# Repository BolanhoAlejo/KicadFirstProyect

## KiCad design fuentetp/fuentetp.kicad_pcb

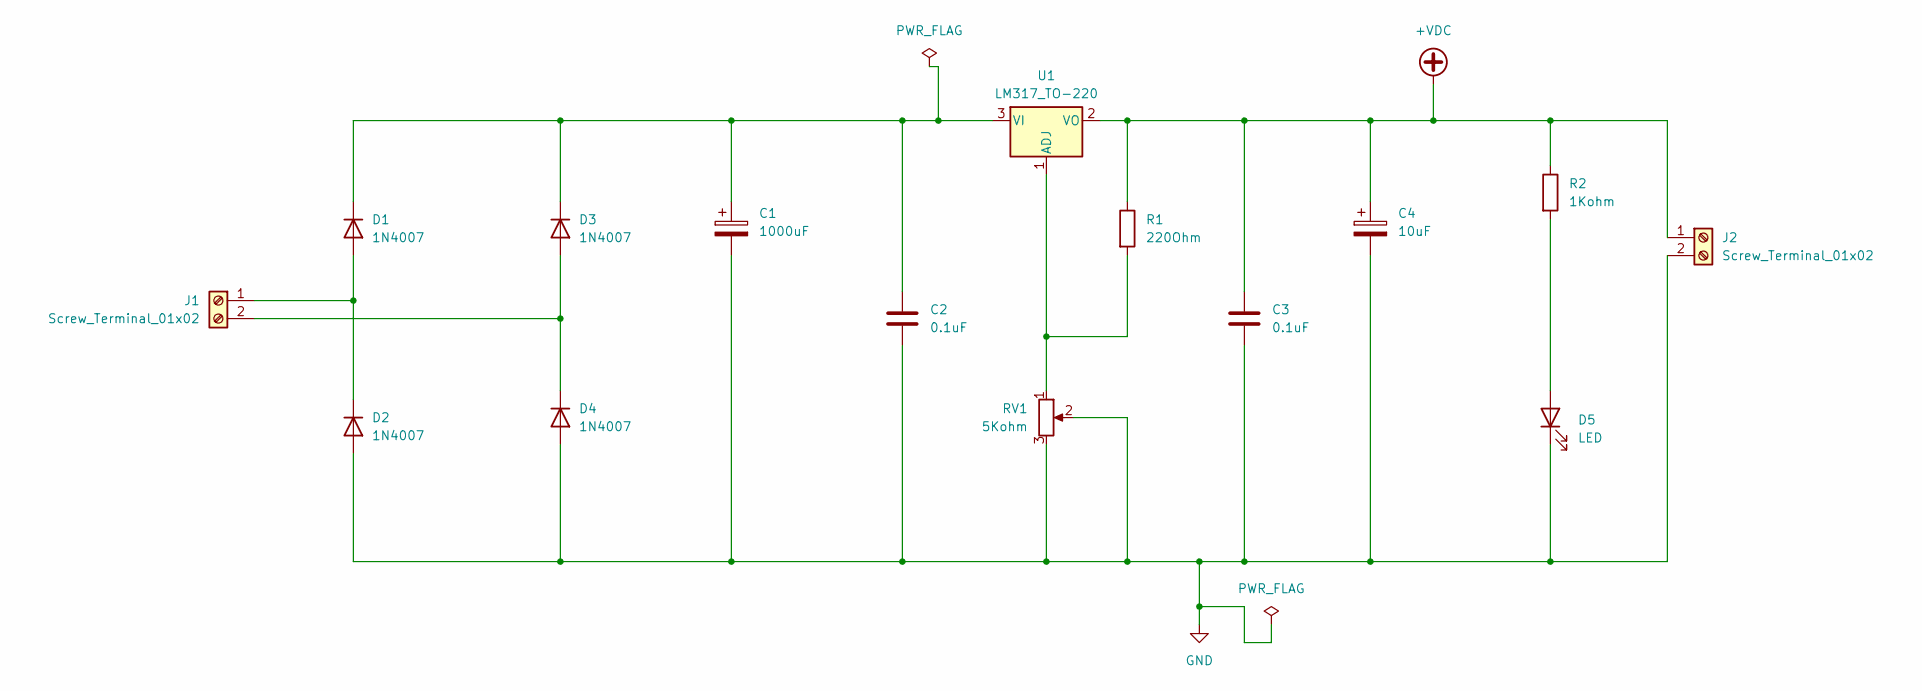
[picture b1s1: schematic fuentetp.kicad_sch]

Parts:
C1: 1000uF; CP_Radial_D10.0mm_P2.50mm
C2, C3: 0.1uF; C_Disc_D4.7mm_W2.5mm_P5.00mm
C4: 10uF; CP_Radial_D4.0mm_P2.00mm
D1, D2, D3, D4: 1N4007; D_DO-41_SOD81_P10.16mm_Horizontal
D5: LED; LED_D5.0mm
J1, J2: Screw_Terminal_01x02; Altech_AK300_1x02_P5.00mm_45-Degree
R1: 220Ohm; R_Axial_DIN0207_L6.3mm_D2.5mm_P10.16mm_Horizontal
R2: 1Kohm; R_Axial_DIN0207_L6.3mm_D2.5mm_P10.16mm_Horizontal
RV1: 5Kohm; Potentiometer_Bourns_3296W_Vertical
U1: LM317_TO-220; TO-220-3_Horizontal_TabDown

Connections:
+VDC: C3.1, C4.1, J2.1, R1.1, R2.1, U1.2 (VO)
GND: C1.2, C2.2, C3.2, C4.2, D2.2 (A), D4.2 (A), D5.1 (K), J2.2, RV1.2, RV1.3
unnamed: D1.2 (A), D2.1 (K), J1.1
unnamed: C1.1, C2.1, D1.1 (K), D3.1 (K), U1.3 (VI)
unnamed: D3.2 (A), D4.1 (K), J1.2
unnamed: D5.2 (A), R2.2
unnamed: R1.2, RV1.1, U1.1 (ADJ)

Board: 2 copper layers, 15 parts (0 on the bottom side), 7 nets, no tracks yet.

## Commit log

2025-09-25 Create notes
